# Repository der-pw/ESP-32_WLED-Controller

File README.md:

# ESP-32_WLED-Controller  

[deutsche Version unten ->](#Deutsch)

### tl;dr
let's talk about [maximum ratings](./maximum_ratings.md)

This is like an evolution of my [ESP-12-WLED_Controller](https://github.com/der-pw/ESP-12_WLED-Controller). It based on my ESP-12 Controller, so you can find also all the necessary information about MOSFETs, etc. there as well.

The version with ESP32 is more powerful and enables features like Sound Reactive https://github.com/atuline/WLED with significantly better performance than the ESP2866. Also you can find here the [Sound Reactive Addon](ESP-32_WLED-Controller_Addon) for this controller. The PCB size has just slightly increased, and the controller can still fit into small projects. To have a clean design and ensure the LED strip works with a 5V data level, I used a 74LVC1G125 as a Logic Level Shifter.

Additionally, the power supply for the LED strip can be turned off by using a P-channel MOSFET. Even when turned off, NEOPIXEL strips consume some power (approximately 1mA per pixel). Luckily, WLED provides an option to control a "Relay" through a user-defined pin. I use an IRF7410 (MOSFET P-channel -12 V -16A SO-8) which can switch max 16A. Additional to the P-MOSFET, there is another N-MOSFET. It works as a driver to switch the P-MOSFET with a 5V logic level and also as an inverter, allowing the main MOSFET to logical "active HIGH" at GPIO12 of the ESP.

## Settings
The configuration for inputs and outputs is as follows:

Label | GPIO | Remarks
--- | --- | ---
Data Pin | `GPIO 2`  
Relay Pin | `GPIO12` | **invert**  
*optional:*  
Button 0 | `GPIO32`  
Button 1 | `GPIO33`  
ADC | `GPIO36` | Analog Input

## Flashing the Firmware

Connect an FTDI or another compatible UART converter like showing the wiring diagram. Either connect with the FLASH button pressed or, if the controller is already powered by a power supply, hold FLASH, press RESET briefly, and then release FLASH. Now controller is in bootloader mode.

The ESP32 may be underpowered by the FTDI, causing the Brownout Detection is triggered. Therefore, you need to power the controller with an external 5V voltage source.

This controller can be used with a [pre-made binary](https://install.wled.me/).

## Strip and Power Supply

Connect the LED strip and power supply as per the wiring diagram.

## Parts List and BOM
| Designator      | Footprint                                  | Quantity | Value        | Info |
|---|---|----|----|----|
| C1, C5        | 0805                                      | 2        | 10µF         |      |
| C2              | 0805                                      | 1        | 47µF         |      |
| C3              | 1206                                      | 1        | 100µF        |      |
| C4              | 0805                                      | 1        | 100nF        |      |
| D1              | D_SMA_Handsoldering                       | 1        | Flyback diode|      |
| Q1              | SOIC-8_3.9x4.9mm_P1.27mm                   | 1        | IRF7410      |      |
| Q2              | SOT-23                                    | 1        | IRLML6344    |      |
| R1, R2, R3, R5| 0805                                      | 4        | 10k          |      |
| R4, R6        | 0805                                      | 2        | 300R         |      |
| SW1             | SW_Push_SPST_NO_Alps_SKRK_handsolder       | 1        | Reset        |      |
| SW2             | SW_Push_SPST_NO_Alps_SKRK_handsolder       | 1        | Flash        |      |
| U1              | SOT-223-3_TabPin2                         | 1        | AMS1117-3.3  |      |
| U2              | SOT-23-5_HandSoldering                    | 1        | 74LVC1G125   |      |
| U3              | ESP32-WROOM-32                            | 1        | ESP32-WROOM-32|      |

Includes parts that need to be soldered by hand.

Quantity | Description | Info
-------- | -------- | --------
1   | CTB1202-5BK   | [Solderable Screw Terminal - 5-pin, Pitch 5 mm](https://www.reichelt.de/loetbare-schraubklemme-5-pol-rm-5-mm-90--ctb1202-5bk-p292662.html)
1   | NHG-A 1.0M 6.3   | [Capacitor, radial, 1000µF, 6.3V, Pitch 3.5mm](https://www.reichelt.de/elko-radial-1-000-f-6-3v-rm3-5-1000h-105-c-20--nhg-a-1-0m-6-3-p200391.html)

## Case

There is also a simple case available. Both parts can be connected with a click fastener. The STEP file for modifications to the case is included in the project folder.

## Gerbers
You can find the necessary fabrication data in the “gerber” folder. This also includes the BOM and CPL files. I have had good experiences with JLCPCB, and production there ran smoothly with the data. However, some parts may not always be available.

## Thank You!
A special thanks to [Aircoookie](https://github.com/Aircoookie) and all those involved in the [WLED](https://github.com/Aircoookie/WLED) project!  
Gerber and fabrication data were created using the [Fabrication Toolkit](https://github.com/bennymeg/JLC-Plugin-for-KiCad).

---
## Deutsch

Dies ist die Weiterentwicklung meines [ESP-12-WLED_Controllers](https://github.com/der-pw/ESP-12_WLED-Controller). Daher kannst du alle nötigen Infos über MOSFET etc. auch dort finden.  
Die Version mit ESP32 ist leistungfähiger und ermöglicht bswp. Sound Reactive Features https://github.com/atuline/WLED. Dafür findes du auch hier ein [Sound Reactive Addon](ESP-32_WLED-Controller_Addon), welches einfach auf den Controller gesteckt werden kann. Die Platinengröße ist nur minimal gewachsen, der Controller lässt sich nach wie vor in kleinen Projekten unterbringen. Für ein sauberes Design und damit der LED-Strip mit einem 5V Datenpegel arbeitet verwende ich einen 74LVC1G125 als Logic Level Shifter.  
Zusätzlich kann die Versorgungsspannung für den LED-Strip über einen P-Kanal MOSFET abgeschaltet werden. Auch im ausgeschalteten Zustand verbrauchen die NEOPIXEL-Strips nämlich Strom (ca. 1mA/Pixel). Ich verwende einen IRF7410 (MOSFET P-Kanal -12 V -16A SO-8) dieser kann max 16A schalten.
Praktischerweise bietet WLED hier die Möglichkeit über einen frei definierten Pin ein "Relay" zu schalten. Vor dem P-MOSFET sitzt ein weiterer N-MOSFET. Einmal funktioniert dieser als Treiber um den P-MOSFET mit 5V Logikpegel zu schalten und zum anderen als Inverter, damit der Haupt-MOSFET praktisch "active HIGH" am GPIO12 des ESP durchschaltet. 

## Einstellungen
Die Konfiguration für Ein-/ und Ausgänge erfolgt wie abgebildet.  

Bezeichnung | GPIO | Bemerkung
--- | --- | ---
Data Pin | `GPIO 2`  
Relay Pin | `GPIO12` | **invert**  
*optional:*  
Button 0 | `GPIO32`  
Button 1 | `GPIO33`  
ADC | `GPIO36` | Analog Eingang

## Firmware flashen

FTDI oder anderen passenden UART-Wandler gemäß Anschlussplan verbinden.
Entweder mit gedrücktem FLASH Button verbinden oder wenn der Controller bereits über ein Netzteil versorgt wirden, FLASH gedrückt halten, RESET kurz drücken und danach kann FLASH losgelassen werden.  

Möglicherweise wird der ESP32 vom FTDI unterversorgt und die Brownout Detection reagiert. Daher ist es ratsam, den Controller bereits mit einer externen 5V Spannungsquelle zu versorgen.  

Dieser Controller kann mit einem [fertigen Binary](https://install.wled.me/) verwendet werden.

## Strip und Versorgungsspannung
  
LED Strip und Netzteil werden gemäß Anschlussplan verbunden.

## Teileliste und BOM
| Designator      | Footprint                                  | Quantity | Value        | Info |
|---|---|----|----|----|
| C1, C5        | 0805                                      | 2        | 10µF         |      |
| C2              | 0805                                      | 1        | 47µF         |      |
| C3              | 1206                                      | 1        | 100µF        |      |
| C4              | 0805                                      | 1        | 100nF        |      |
| D1              | D_SMA_Handsoldering                       | 1        | Flyback diode|      |
| Q1              | SOIC-8_3.9x4.9mm_P1.27mm                   | 1        | IRF7410      |      |
| Q2              | SOT-23                                    | 1        | IRLML6344    |      |
| R1, R2, R3, R5| 0805                                      | 4        | 10k          |      |
| R4, R6        | 0805                                      | 2        | 300R         |      |
| SW1             | SW_Push_SPST_NO_Alps_SKRK_handsolder       | 1        | Reset        |      |
| SW2             | SW_Push_SPST_NO_Alps_SKRK_handsolder       | 1        | Flash        |      |
| U1              | SOT-223-3_TabPin2                         | 1        | AMS1117-3.3  |      |
| U2              | SOT-23-5_HandSoldering                    | 1        | 74LVC1G125   |      |
| U3              | ESP32-WROOM-32                            | 1        | ESP32-WROOM-32|      |

Beinhaltet Teile, die von Hand eingelötet werden müssen.
Anzahl | Beschreibung | Info
-------- | -------- | --------
1   | CTB1202-5BK   | [Lötbare Schraubklemme - 5-pol, RM 5 mm](https://www.reichelt.de/loetbare-schraubklemme-5-pol-rm-5-mm-90--ctb1202-5bk-p292662.html)
1   | NHG-A 1,0M 6,3   | [Elko, radial, 1.000µF, 6,3V, RM3,5](https://www.reichelt.de/elko-radial-1-000-f-6-3v-rm3-5-1000h-105-c-20--nhg-a-1-0m-6-3-p200391.html)

## Gehäuse

Ein einfaches Gehäuse gibt es auch.
Beide Teile können über einen Klickverschluss miteinander verbunden werden.
Für Änderungen am Gehäuse liegt im Projektorder die STEP-Datei.  

## Gerberdaten
Du kann die nötigen Fertigungsdaten im Ordner "gerber" finden. Darin enthalten sind auch die BOM und CPL Files. Mit JLCPCB habe ich guter Erfahrungen gemacht, und mit den Daten lief die Fertigung dort auch problemlos. Es ist jedoch möglich, das manche Teile vielleicht nicht immer verfügbar sind.

## Dankeschön!  
Ganz besonderer Dank geht an [Aircoookie](https://github.com/Aircoookie) und alle Beteiligten, die am [WLED](https://github.com/Aircoookie/WLED) Projekt mitarbeiten!  
Gerber und Fertigungsdaten wurden mit [Fabrication Toolkit](https://github.com/bennymeg/JLC-Plugin-for-KiCad) erstellt!

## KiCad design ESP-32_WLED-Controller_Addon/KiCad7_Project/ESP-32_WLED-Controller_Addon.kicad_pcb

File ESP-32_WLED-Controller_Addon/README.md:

# ESP-32_WLED-Controller_addon  

[deutsche Version unten ->](#Deutsch)

This addon board allows you to expand the ESP-32_WLED-Controller with the Sound Reactive feature https://github.com/atuline/WLED. The board is practically stacked on top of the controller using 2.54mm pin and socket headers.

## Settings

WLED Sound Reactive comes with an additional configuration menu.
For Squelch and Gain, you'll need to configure your own settings.
Microphone type is **Generic Analog**.
The Analog Input Pin is on `GPIO36`.

## Case

There is also a simple case available for connecting the 3.5mm audio jack.
The STEP file for further modifications is also located in the "case" folder.

## BOM

| Refs | Qty | Component | Description |
| --- | --- | --- | ----------- |
| R1, R2 | 2 | 680R | Resistor 0805  |
| R3, R4 | 2 | 1M | Resistor 0805  |
| C1, C2 | 2 | 100nF | Capacitor 0805  |
| J3 | 1 | Audio Jack 3.5mm | PJ230D https://de.aliexpress.com/item/4000661908135.html |
| J1 | 1 | PinHeader_1x05_P2.54mm_Vertical |
| J5 | 1 | PinHeader_1x04_P2.54mm_Vertical |

## Gerber Data

You can find the manufacturing data for the board in the “gerber” folder.
In addition, there is also the BOM and CPL data for SMT production. However, the assembly is two-sided, as the jack socket is mounted on the bottom for space reasons.
The jack socket is called PJ230D. I found these cheaply at https://de.aliexpress.com/item/4000661908135.html.

---
## Deutsch

Mit dieser Addon-Platine lässt sich der ESP-32_WLED-Controller um das Sound Reactive Feature erweitern https://github.com/atuline/WLED. Die Platine wird praktisch im "Huckepack" auf den Controller gesteckt.
Dazu lassen sich 2.54mm Stift- und Buchsenleisten verwenden.

## Einstellungen

WLED Soundreactive hat ein weiteres Konfigurationsmenü.
Für Squelch und Gain muss man seine eigenen Einstellungen fingen.
Micropone type ist **Generic Analog**.  
Der Analog Input Pin liegt auf `GPIO36`.

## Gehäuse

Es gibt auch ein einfaches Gehäuse, damit man den 3,5mm Klinkenstecker anschließen kann.
Die STEP-Datei für weitere Modifikationen befindet sich auch in dem Ordner "case" 

## BOM

| Refs | Qty | Component | Description |
| --- | --- | --- | ----------- |
| R1, R2 | 2 | 680R | Resistor 0805  |
| R3, R4 | 2 | 1M | Resistor 0805  |
| C1, C2 | 2 | 100nF | Capacitor 0805  |
| J3 | 1 | Audio Jack 3.5mm | PJ230D https://de.aliexpress.com/item/4000661908135.html |
| J1 | 1 | PinHeader_1x05_P2.54mm_Vertical |
| J5 | 1 | PinHeader_1x04_P2.54mm_Vertical |

## Gerberdaten

Die Fertigungsdaten zur Platine findest du im Ordner "gerber". 
Zusätzlich gibt es dort auch die BOM und CPL Daten für die SMT-Fetigung. Die Bestückung ist allerdings zweiseitig, da aus Platzgründen die Klinkenbuchse auf der Unterseite montiert wird.
Die Klinkenbuchse heißt PJ230D. Diese habe ich günstig unter https://de.aliexpress.com/item/4000661908135.html gefunden.

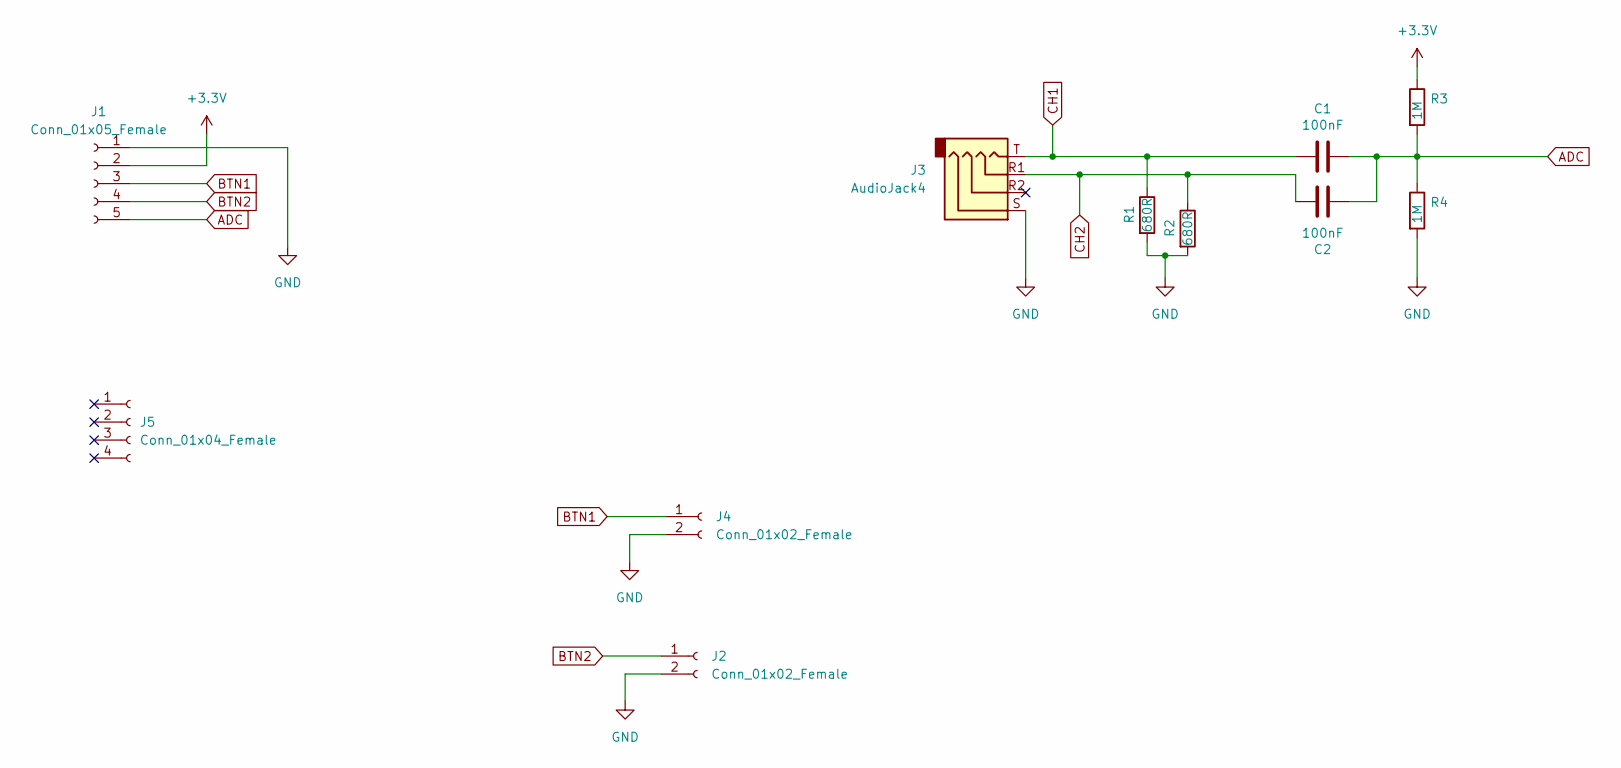
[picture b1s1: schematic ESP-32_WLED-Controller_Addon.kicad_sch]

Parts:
C1, C2: 100nF; C_0805_2012Metric_Pad1.18x1.45mm_HandSolder; LCSC C49678
J1: Conn_01x05_Female; PinHeader_1x05_P2.54mm_Vertical
J2, J4: Conn_01x02_Female; PinHeader_1x02_P2.54mm_Vertical
J3: AudioJack4; Jack_3.5mm_PJ320D_Horizontal
J5: Conn_01x04_Female; PinHeader_1x04_P2.54mm_Vertical
R1, R2: 680R; R_0805_2012Metric_Pad1.20x1.40mm_HandSolder; LCSC C17798
R3, R4: 1M; R_0805_2012Metric_Pad1.20x1.40mm_HandSolder; LCSC C17514

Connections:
+3V3: J1.2, R3.1
ADC: C1.2, C2.1, J1.5, R3.2, R4.1
BTN1: J1.3, J4.1
BTN2: J1.4, J2.1
CH1: C1.1, J3.T, R1.1
CH2: C2.2, J3.R1, R2.1
GND: J1.1, J2.2, J3.S, J4.2, R1.2, R2.2, R4.2

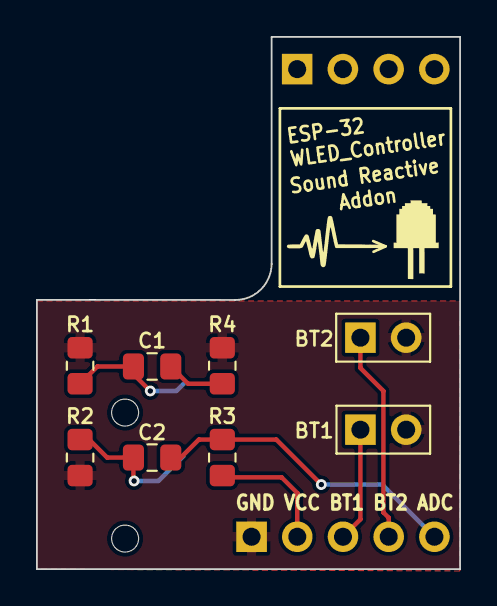
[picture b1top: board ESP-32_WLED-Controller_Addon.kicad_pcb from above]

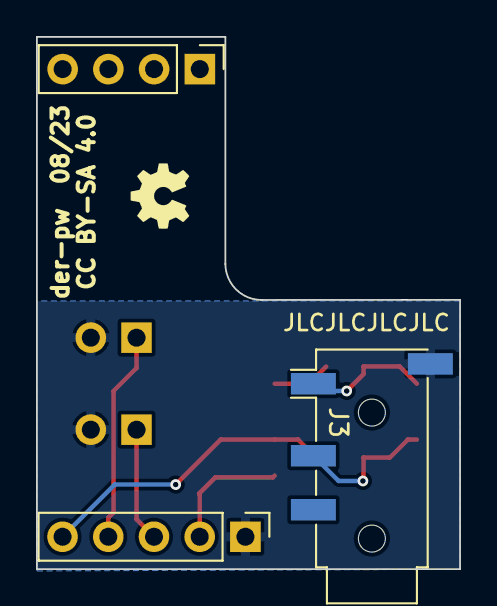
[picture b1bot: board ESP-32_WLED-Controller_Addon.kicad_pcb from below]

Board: 2 copper layers, 23.5 x 29.6 mm, 11 parts (3 on the bottom side), 7 nets.

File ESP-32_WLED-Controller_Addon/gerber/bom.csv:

Designator,Footprint,Quantity,Value,LCSC Part #
"C1, C2",0805,2,100nF,C49678
J3,Jack_3.5mm_PJ320D_Horizontal,1,AudioJack4,
"R1, R2",0805,2,680R,C17798
"R3, R4",0805,2,1M,C17514

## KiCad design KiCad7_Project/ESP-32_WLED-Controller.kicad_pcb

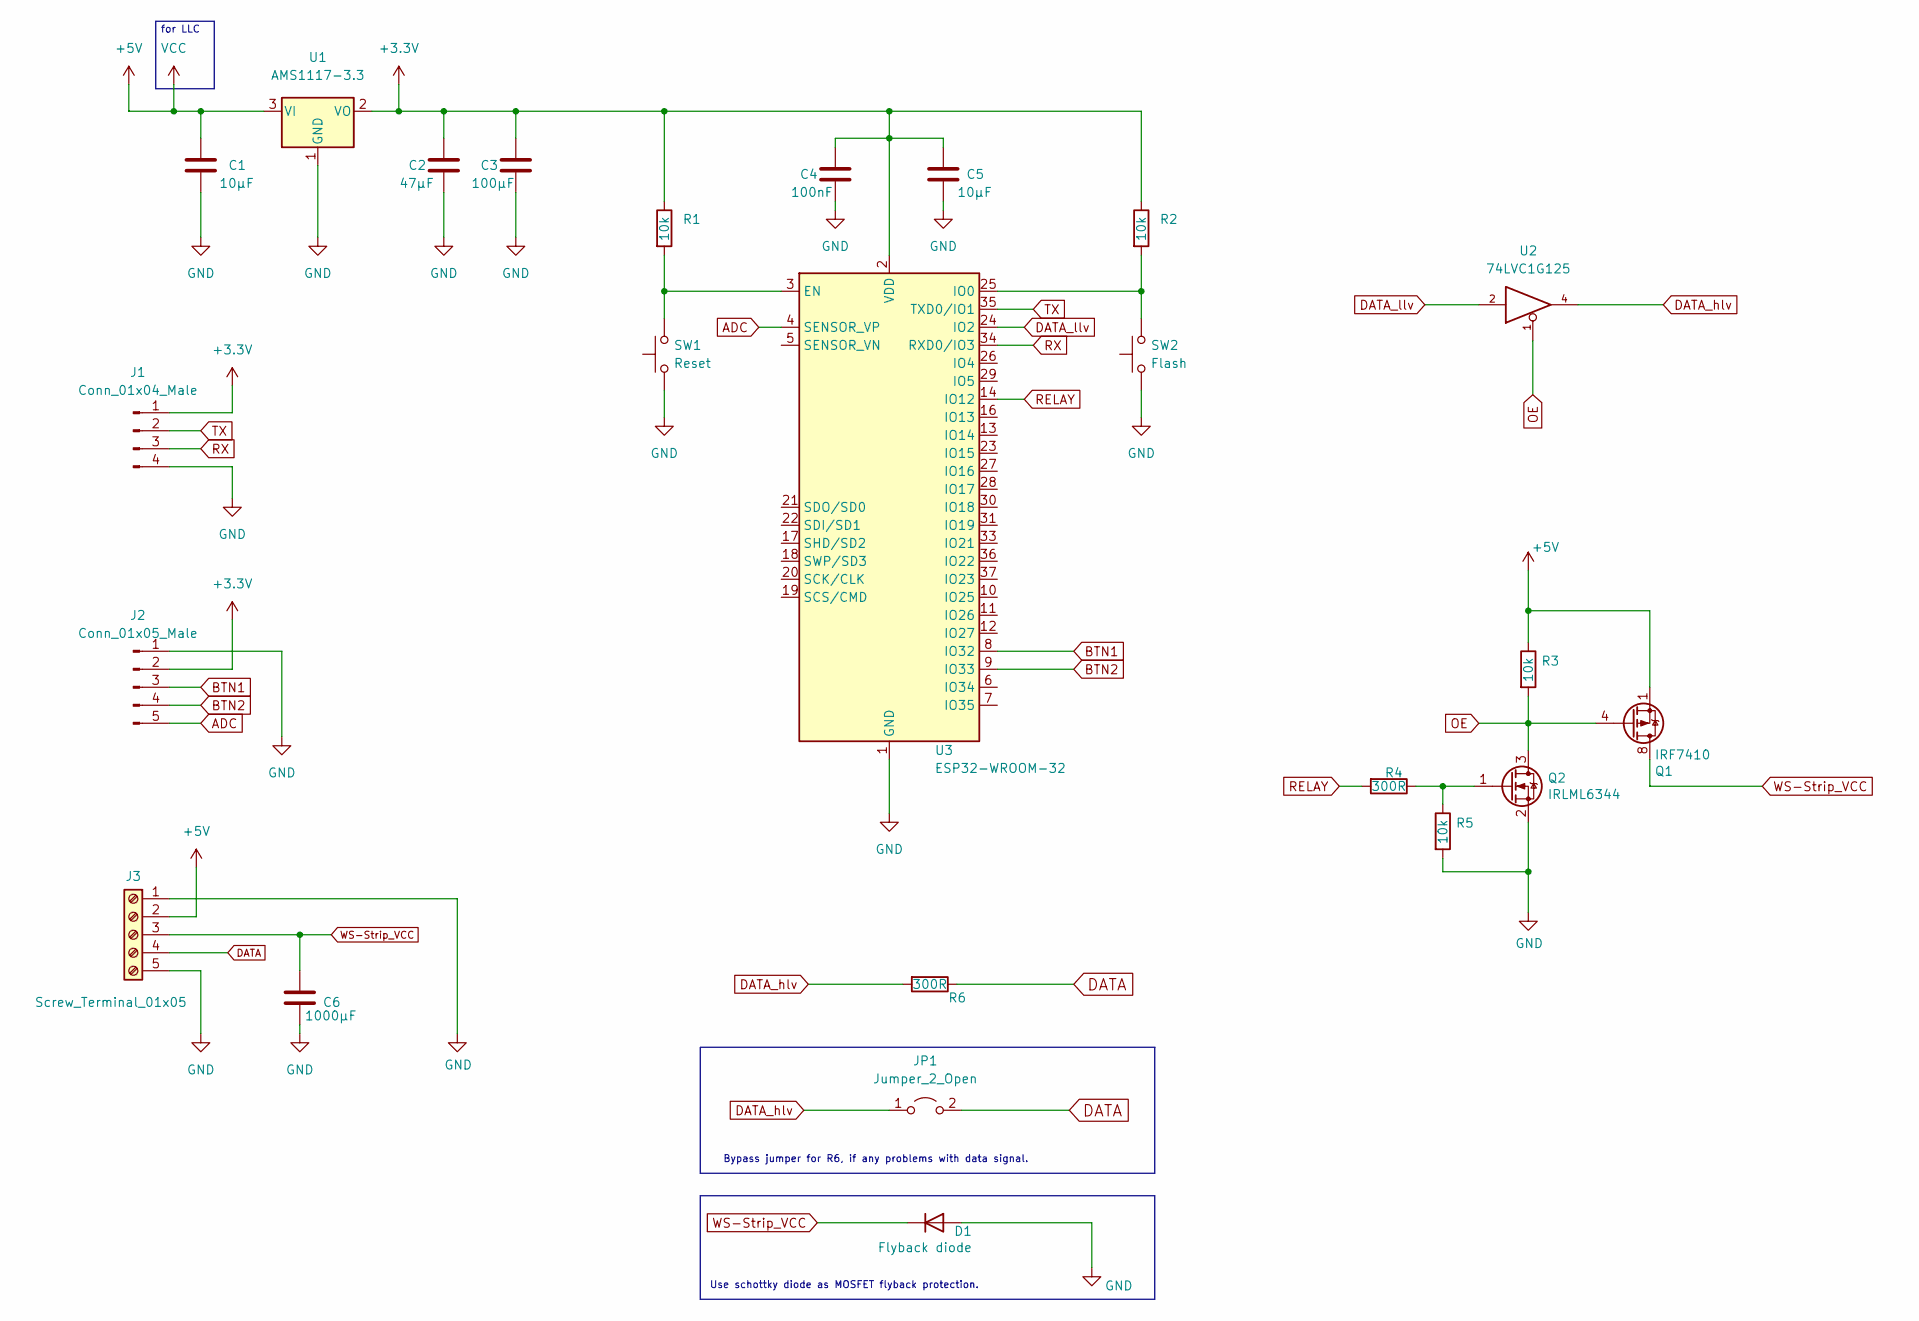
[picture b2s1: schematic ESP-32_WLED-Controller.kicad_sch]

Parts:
C1, C5: 10µF; C_0805_2012Metric_Pad1.18x1.45mm_HandSolder; LCSC C15850
C2: 47µF; C_0805_2012Metric_Pad1.18x1.45mm_HandSolder; LCSC C16780
C3: 100µF; C_1206_3216Metric_Pad1.33x1.80mm_HandSolder; LCSC C15008
C4: 100nF; C_0805_2012Metric_Pad1.18x1.45mm_HandSolder; LCSC C49678
C6: 1000µF; CP_Radial_D8.0mm_P3.50mm; LCSC C189254
D1: Flyback diode; D_SMA_Handsoldering; LCSC C2480
J1: Conn_01x04_Male; PinSocket_1x04_P2.54mm_Vertical
J2: Conn_01x05_Male; PinSocket_1x05_P2.54mm_Vertical
J3: Screw_Terminal_01x05; TerminalBlock_bornier-5_P5.08mm
JP1: Jumper_2_Open; SolderJumper-2_P1.3mm_Open_RoundedPad1.0x1.5mm
Q1: IRF7410; SOIC-8_3.9x4.9mm_P1.27mm; LCSC C148144
Q2: IRLML6344; SOT-23; LCSC C53550
R1, R2, R3, R5: 10k; R_0805_2012Metric_Pad1.20x1.40mm_HandSolder; LCSC C17414
R4, R6: 300R; R_0805_2012Metric_Pad1.20x1.40mm_HandSolder; LCSC C17617
SW1: Reset; SW_Push_SPST_NO_Alps_SKRK_handsolder; LCSC C843669
SW2: Flash; SW_Push_SPST_NO_Alps_SKRK_handsolder; LCSC C843669
U1: AMS1117-3.3; SOT-223-3_TabPin2; LCSC C6186
U2: 74LVC1G125; SOT-23-5_HandSoldering; LCSC C23654
U3: ESP32-WROOM-32; LCSC C82899

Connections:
+3V3: C2.1, C3.1, C4.1, C5.1, J1.1, J2.2, R1.1, R2.1, U1.2 (VO), U3.2 (VDD)
+5V: C1.1, J3.2, Q1.1 (S), Q1.2 (S), Q1.3 (S), R3.1, U1.3 (VI), U2.5 (VCC)
ADC: J2.5, U3.4 (SENSOR_VP)
BTN1: J2.3, U3.8 (IO32)
BTN2: J2.4, U3.9 (IO33)
DATA: J3.4, JP1.2 (B), R6.1
DATA_hlv: JP1.1 (A), R6.2, U2.4
DATA_llv: U2.2, U3.24 (IO2)
GND: C1.2, C2.2, C3.2, C4.2, C5.2, C6.2, D1.2 (A), J1.4, J2.1, J3.1, J3.5, Q2.2 (S), R5.2, SW1.1, SW2.1, U1.1 (GND), U2.3 (GND), U3.1 (GND), U3.15 (GND), U3.38 (GND), U3.39 (GND)
unnamed: Q2.1 (G), R4.1, R5.1
unnamed: R1.2, SW1.2, U3.3 (EN)
unnamed: R2.2, SW2.2, U3.25 (IO0)
OE: Q1.4 (G), Q2.3 (D), R3.2, U2.1
RELAY: R4.2, U3.14 (IO12)
RX: J1.3, U3.34 (RXD0/IO3)
TX: J1.2, U3.35 (TXD0/IO1)
WS-Strip_VCC: C6.1, D1.1 (K), J3.3, Q1.5 (D), Q1.6 (D), Q1.7 (D), Q1.8 (D)

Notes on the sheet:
for LLC
Use schottky diode as MOSFET flyback protection.
Bypass jumper for R6, if any problems with data signal.

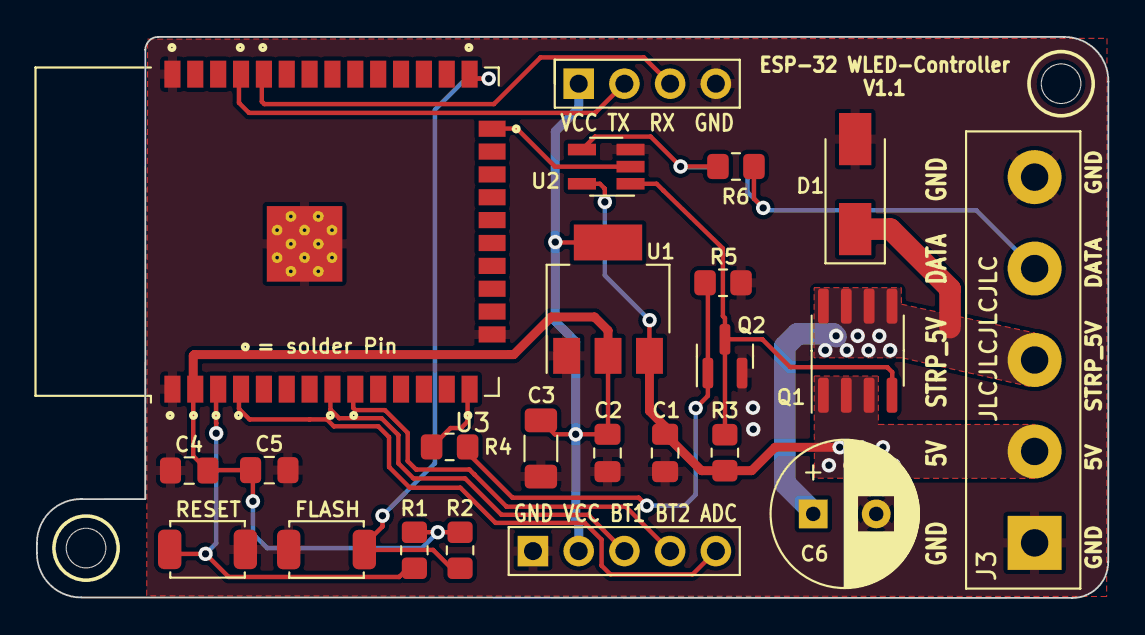
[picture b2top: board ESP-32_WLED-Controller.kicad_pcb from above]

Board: 2 copper layers, 59.5 x 31.2 mm, 24 parts (1 on the bottom side), 17 nets.

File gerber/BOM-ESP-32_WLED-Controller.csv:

Comment,Designator,Footprint,LCSC
IRF7410,Q1,SOIC-8_3.9x4.9mm_P1.27mm,C148144
100µF,C3,C_1206_3216Metric_Pad1.33x1.80mm_HandSolder,C15008
10µF,"C1,C5",C_0805_2012Metric_Pad1.18x1.45mm_HandSolder,C15850
47µF,C2,C_0805_2012Metric_Pad1.18x1.45mm_HandSolder,C16780
10k,"R1,R2,R3,R5",R_0805_2012Metric_Pad1.20x1.40mm_HandSolder,C17414
300R,"R4,R6",R_0805_2012Metric_Pad1.20x1.40mm_HandSolder,C17617
74LVC1G125,U2,SOT-23-5_HandSoldering,C23654
Flyback diode,D1,D_SMA_Handsoldering,C2480
100nF,C4,C_0805_2012Metric_Pad1.18x1.45mm_HandSolder,C49678
IRLML6344,Q2,SOT-23,C53550
AMS1117-3.3,U1,SOT-223-3_TabPin2,C6186
ESP32-WROOM-32,U3,ESP32-WROOM-32,C82899
Reset,"SW1,SW2",SW_Push_SPST_NO_Alps_SKRK_handsolder,C843669

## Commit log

2022-01-20 first infos
2023-08-16 Upload gerbers and project folder
2023-08-16 BOM and CPL
2023-09-17 finalize this repo to PCB V1.1 incl. SR addon
2023-09-17 fixed small typos
2023-09-25 add maximum ratings
2023-09-26 update readme addon
2023-10-07 fixed small issues in BOM
2024-04-14 small typos
2024-04-15 clenaup

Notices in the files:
ESP-32_WLED-Controller_Addon/KiCad7_Project/ESP-32_WLED-Controller_Addon.kicad_pcb:
CC BY-SA 4.0
ESP-32_WLED-Controller_Addon/README.md:
License: CC BY-SA 4.0
